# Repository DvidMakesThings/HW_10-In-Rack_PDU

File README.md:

# ENERGIS - The Managed PDU Project for 10-Inch Rack

## Overview

The **10-Inch Rack PDU (Power Distribution Unit)** is a modular power management system designed for efficient control and monitoring of power in a
rack-mounted environment. The project includes a Main Board and a display board to handle switching and power management.

Update 05.2025: Since lot of people said, it would be nice to have a Non-230V-Version, I started to develop
the USB-C version of ENERGIS with USB PD Source functionality: [PDNode-600 Pro](https://github.com/DvidMakesThings/HW_PDNode-600-Pro)

## ENERGIS Video Series

A new ENERGIS video series is rolling out. Part 1 is live below; Parts 2–4 will follow soon.

| Part | Title | Video |
| --- | --- | :---: |
| 1 | Overview |  |
| 2 | Hardware deep dive - The Schematics |  |
| 3 | Hardware deep dive - PCB design and Assembly | Coming soon |
| 4 | Embedded development - firmware and interfaces | Coming soon |
| 5 | Testing and validation | Coming soon |

## Progress and news

### Latest Features

| Feature                   | Description                                                           | Status | Note |
| ---                       | ---                                                                   | --- | --- |
| Renamebable Channels      | Channels are marked as 1–8; add label functionality                   |  | See: [Control page](#control-page) |
| Preset features           | ENERGIS now offers 5 programmable presets to apply on output          |  | See: [Settings page](#settings-page) |
| Apply-On-Startup feature  | A saved preset can be set to be auto-applied on device startup        |  | See: [Settings page](#settings-page) |
| Offset Calibration        | Implement off-state auto-zero for 0.75–0.77V and 0.02–0.05A offsets   |  | - |
| Safety features           | Software based current limit and restricion policy implemented        |  | - |
| Sheet metal enclosure     | Manufacturing and assembly ready. No future revision for enclosure    |  | - |

### Currently working on

| Improvement               | Description                                                       | Status |
| ---                       | ---                                                               | --- |
| Production optimization   | Finalize assembly workflow and cost reduction                     |  |
| Extended testing          | Expand automated test coverage (I²C, SPI, long-term soak tests)   |  |
| Community feedback        | Incorporate suggestions and adapt design for wider use cases      |  |
| And even more debugging   | It survived the 24h test, but you can never test enough           |  |

### Development Phases (Hardware + Firmware)

| Hardware Phase                          | Status         | Firmware Phase                         | Status         |
| --------------------------------------- | -------------- | -------------------------------------- | -------------- |
| PCB Design for Rev1.0                   | ✅ Completed    | CONFIG file for HW description         | ✅ Completed    |
| Enclosure Design                        | ✅ Completed    | ILI4988 TFT LCD Driver                 | ✅ Completed    |
| Order PCB                               | ✅ Completed    | MCP23017 Display-Board Driver          | ✅ Completed    |
| Prototyping and Hardware Testing        | ✅ Completed    | MCP23017 Relay-Board Driver            | ✅ Completed    |
| Implementing Rev2.0                     | ✅ Completed    | W5500 Ethernet Driver                  | ✅ Completed    |
| Implementing Relay Board Rev2.1         | ✅ Completed    | CAT24C512 512K EEPROM Driver           | ✅ Completed    |
| Initial Firmware Development            | ✅ Completed    | Version Control and EEPROM Data        | ✅ Completed    |
| Final PCB Revision                      | ✅ Completed    | Display Functions                      | ✅ Completed    |
| Enclosure Testing & Ventilation         | ✅ Completed    | System Startup Script                  | ✅ Completed    |
| Power Monitoring                        | ✅ Completed    | Multicore processing and RTOS          | ✅ Completed    |
| Production Optimization                 | 🔵 Planned      | Pushbutton control                     | ✅ Completed    |
| -                                       | -               | HLW8032 Power Monitor Dirver           | ✅ Completed    |
| -                                       | -               | Make Everything work together          | ✅ Completed    |
| -                                       | -               | HTML Server Implementation             | ✅ Completed    |
| -                                       | -               | Software debugging                     | ✅ Completed    |
| -                                       | -               | Ethernet based firmware update         | ❌ Not Possible |

---

## Specifications (EU, IEC/ENEC)

### Electrical Characteristics

* **Input:** 230 V AC, **10 A max**
* **Output Voltage:** 230 V AC
* **Total Output Current (all channels combined):** **10 A max**
* **Per-Channel Output Current:** **10 A max per active channel**, with **total combined output limited to 10 A**
* **Internal Power Supply:** 12 V, 1.5 A SMPS
* **Derived Internal Voltages:** 5 V and 3.3 V regulated from 12 V

### Relay Output Ratings

* **Common AC Trace Handling:** 16A max
* **Per-Relay Trace Rating:** 16A max
* **Relay Contact Rating:** 16A max

### Control and Driving Circuit

* **Relay Driver:** ULN2803 Darlington Array
* **Driving Current:** 33 mA per relay

## Specifications (US/Canada, UL/CSA)

### Electrical Characteristics

* **Input:** 250 V AC, **15 A max**
* **Output Voltage:** 250 V AC
* **Total Output Current (all channels combined):** **15 A max**
* **Per-Channel Output Current:** **15 A max per active channel**, with **total combined output limited to 15 A**
* **Internal Power Supply:** 12 V, 1.5 A SMPS
* **Derived Internal Voltages:** 5 V and 3.3 V regulated from 12 V

### Relay Output Ratings

* **Common AC Trace Handling:** 16 A max
* **Per-Relay Trace Rating:** 16 A max
* **Relay Contact Rating:** 16 A max

### Control and Driving Circuit

* **Relay Driver:** ULN2803 Darlington Array
* **Driving Current:** 33 mA per relay

---

## Features

- **Main Board:** Handles Ethernet communication, power conversion, and system logic. Manages AC switching with 8x 230V relays and safety
  isolation.
- **Display Board:** Headless mode, possible manual control with push buttons and real-time LED feedback
- **Ethernet Connectivity:** Uses the W5500 SPI-based Ethernet chip for remote
  control and monitoring via SNMPv1 and/or Web-UI. Supports DHCP with automatic
  link-local fallback and zero-config discovery by name (`energis.local` / `energis`)
  via mDNS and NetBIOS; IP changes apply live without a reboot.
- **Power Measurement:** AC voltage and current sensing for monitoring.
- **Sheetmetal Enclosure:** Designed for 10-inch rack mounting with front and rear access.

--- 

## Schematics

The full schematics for each board are available:

- **[Main Board Schematics](src/PDF/ENERGIS-1.1.0_mainBoard_schematics.pdf)**
- **[Display Board Schematics](src/PDF/ENERGIS-1.1.0_displayBoard_schematics.pdf)**

---

## Hardware Stackup

<table>
  <tr>
    <td align="center">
      
      <br><b>Main Board Top</b>
    </td>
    <td align="center">
      
      <br><b>Main Board Bottom</b>
    </td>
  </tr>
  <tr>
    <td align="center">
      
      <br><b>Display Board Top</b>
    </td>
    <td align="center">
      
      <br><b>Display Board Bottom</b>
    </td>
  </tr>
  <tr>
    <td align="center">
      
      <br><b>PEM Adapter</b>
    </td>
    <td align="center">
      
      <br><b>PEM Adapter</b>
    </td>
  </tr>
</table>

## Enclosure

The **Energis** PDU enclosure is built from **Aluminum 5052 sheet metal** with a thickness of **1.5 mm**, ensuring both durability and lightweight construction. It follows a **10-inch rack form factor (1U height)** with custom mounting brackets and integrated cutouts for AC input, Ethernet, USB-C, status LEDs, and IEC outlets.

Key specifications:
* **Material:** Aluminum 5052, 1.5 mm
* **Finish:** Powder coat (matte black, process black)
* **Threads & tapped holes:** Yes (no inserts, no welding)
* **Marking:** Laser engraved front and back panel labeling
* **Design:** Precision CNC cut and bent sheet metal, matte black powder-coated for protection and aesthetics

<br></br>
<div style="display: flex; gap: 24px; justify-content: center; align-items: flex-start; margin-bottom: 24px;">

</div>

<br></br>
Mounting options:
* **Desktop use** without brackets  
* **10-inch rack mounting** 

---

## Web UI

The ENERGIS now includes a lightweight embedded Web-UI for configuration and control.

## Control page

## Settings page

---

## Tests

Automated hardware and firmware validation is now integrated into **ENERGIS**.  
Test reports are published through **GitHub Pages** for transparent, reproducible verification.

All tests are executed using my **Universal Test Framework (UTFW)**, a custom Python-based automation framework, developed for hardware and firmware validation.  
UTFW provides deterministic test sequencing, automated setup and teardown, structured logging, analysis, and unified HTML/XML reporting.  
The nightly regression runs every individual test together to verify overall system stability and catch integration issues early.

---

### Nightly Regression Suite
Comprehensive end-to-end system test covering:
- UART communication  
- SNMP protocol  
- Web interface (PCAP)  
- EEPROM persistence  
- Power monitoring (HLW8032)  
- ADC/thermal sanity checks  
- Relay stress switching  

**[Latest Regression Report](https://dvidmakesthings.github.io/HW_10-In-Rack_PDU/Tests/Nightly_regression/test_suite_Nightly_Tests_20251005_232014.html)**

---

### Individual Test Reports
- [Serial Communication Test Report (HTML)](https://dvidmakesthings.github.io/HW_10-In-Rack_PDU/Tests/report_tc_serial_utfw/tc_serial_utfw_report.html)
- [Network SNMP Test Report (HTML)](https://dvidmakesthings.github.io/HW_10-In-Rack_PDU/Tests/report_tc_network_snmp/tc_network_snmp_report.html)
- [Network PCAP Analysis Report (HTML)](https://dvidmakesthings.github.io/HW_10-In-Rack_PDU/Tests/report_tc_network_pcap/tc_network_pcap_report.html)
- [PCAP Capture Test Report (HTML)](https://dvidmakesthings.github.io/HW_10-In-Rack_PDU/Tests/report_tc_pcap_capture/tc_pcap_capture_report.html)
- [Power Monitoring Test Report (HLW8032) (HTML)](https://dvidmakesthings.github.io/HW_10-In-Rack_PDU/Tests/report_tc_power_hlw8032/tc_power_hlw8032_report.html)
- [EEPROM Persistence Test Report (HTML)](https://dvidmakesthings.github.io/HW_10-In-Rack_PDU/Tests/report_tc_eeprom_persistence/tc_eeprom_persistence_report.html)
- [Sanity Check Test Report (HTML)](https://dvidmakesthings.github.io/HW_10-In-Rack_PDU/Tests/report_tc_sanity_check/tc_sanity_check_report.html)
- [Relay Stress Switching Test Report (HTML)](https://dvidmakesthings.github.io/HW_10-In-Rack_PDU/Tests/report_tc_stress_switching/tc_stress_switching_report.html)

---

### Changelog:
#### Rev0.1.0:
- Initial desing

#### Rev0.2.0:
- Correct all hardware related bugs
- Display-Board Rev0.2.0: 
    - Buttons too close to each-other. Manual control is uncomfortable 
    - MCP23S17 seems like unreachable, invertory shortage everywhere. Change to MCP23017
- Controller-Board Rev0.2.0: 
    - W5500 crystal wiring bug. 
    - v1.0 connectors replaced to smaller FFC ones
- Relay-Board Rev0.2.0: 
    - Add HLW8032 for power monitoring
    - Replace Flyback converter to a cheaper - ready made AC-DC converter unit

#### Rev0.2.1:
- Relay-Board Rev0.2.1: 
    - Capacitive dropper does not have enough power to supply 8xHLW8032 - Non-Isolated  buck converter implemented
- Display-Board Rev0.2.1:
    - Planned revision without the LCD. This is the main size issue, going to do a version where the setup fits in 1U size. 
    Currently for debug purposes 1.5U is perfectly fine

#### ENERGIS 1.0.0 
- Relay-Board and Controller Board is now combined: Main Board
- Added enable functionality to the PSU
- Added high precision LDO to supply the MCU
- Additional fan is possible, but the temperature doesn't go above 36°C

#### ENERGIS 1.1.0
- Cleaned up routing both for Display- and Main board
- NEW: PEM-Adapter: Unfortunately the commercially available Power Entry Modules are using bussed topology, seems like it's
impossible to buy snap-in modules with individual L/N control. The only possibility I've found is the 3-104-370 from Schurter, but
it's a PCB-mountable version. Using a small adapter board to hook the solder joints to faston connectors seems to be the only possibility

### Firmware Changelog
#### Firmware 1.2.0
- NEW: Live network reconfiguration: IP, subnet, gateway, DNS and DHCP mode changes apply on the fly, no reboot
- NEW: Software DHCP client (DORA) with DHCP hostname registration (option 12)
- NEW: Automatic link-local (APIPA, 169.254.x.y) fallback when DHCP finds no server
- NEW: Zero-config name resolution via mDNS (`energis.local`) and NetBIOS (`energis`)
- NEW: Per-unit unique name derived from the MAC (`energis-<mac>`) to avoid collisions, with the generic `energis` kept as an alias
- Web Settings: DHCP toggle; IP fields grey out when DHCP is enabled
- Console: `SET_DHCP` command; `NETINFO` now reports the live active IP and name
- Fixes: DHCP renewal loop with very long leases; name responders restored after cable re-plug/standby-exit

## License
### Software Components
This project's software is licensed under the **GNU Affero General Public License v3.0 (AGPL-3.0)**.
See the [Software License](LICENSE-AGPL) file for details.

#### What AGPL-3.0 means:

- ✅ **You can** freely use, modify, and distribute this software
- ✅ **You can** use this project for personal, educational, or internal purposes
- ✅ **You can** contribute improvements back to this project

- ⚠️ **You must** share any modifications you make if you distribute the software
- ⚠️ **You must** release the source code if you run a modified version on a server that others interact with
- ⚠️ **You must** keep all copyright notices intact

- ❌ **You cannot** incorporate this code into proprietary software without sharing your source code
- ❌ **You cannot** use this project in a commercial product without either complying with AGPL or obtaining a different license

### Hardware Components
Hardware designs, schematics, and related documentation are licensed under the **Creative Commons Attribution-NonCommercial-ShareAlike 4.0 International License (CC BY-NC-SA 4.0)**. See the [Hardware License](LICENSE-CC-BY-NC-SA) file for details.

#### What CC BY-NC-SA 4.0 means:

- ✅ **You can** study, modify, and distribute the hardware designs
- ✅ **You can** create derivative works for personal, educational, or non-commercial use
- ✅ **You can** build this project for your own personal use

- ⚠️ **You must** give appropriate credit and indicate if changes were made
- ⚠️ **You must** share any modifications under the same license terms
- ⚠️ **You must** include the original license and copyright notices

- ❌ **You cannot** use the designs for commercial purposes without explicit permission
- ❌ **You cannot** manufacture and sell products based on these designs without a commercial license
- ❌ **You cannot** create closed-source derivatives for commercial purposes
- ❌ **You cannot** use the designer's trademarks without permission

### Commercial & Enterprise Use

Commercial use of this project is prohibited without obtaining a separate commercial license. If you are interested in:

- Manufacturing and selling products based on these designs
- Incorporating these designs into commercial products
- Any other commercial applications

Please contact me through any of the channels listed in the [Contact](#contact) section to discuss commercial licensing arrangements. Commercial licenses are available with reasonable terms to support ongoing development.

## Contact

For questions or feedback:
- **Email:** [dvidmakesthings@gmail.com](mailto:dvidmakesthings@gmail.com)
- **GitHub:** [DvidMakesThings](https://github.com/DvidMakesThings)

## Contributing

Contributions are welcome! As this is an early-stage project, please reach out before 
making substantial changes:

1. Fork the repository
2. Create a feature branch (`git checkout -b feature/concept`)
3. Commit your changes (`git commit -m 'Add concept'`)
4. Push to the branch (`git push origin feature/concept`)
5. Open a Pull Request with a detailed description

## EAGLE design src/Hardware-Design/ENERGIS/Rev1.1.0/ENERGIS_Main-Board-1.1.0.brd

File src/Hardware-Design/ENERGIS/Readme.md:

# HLW8032 Upper-Bank Routing Issue — Fixed in HW 1.0.1

## Summary
On **hardware rev 1.0.0**, the measurement path for channels **5–8** is cross-routed at the optocouplers, mirroring the upper nibble. Relays/buttons are unaffected; only measurement presentation would be wrong without compensation.

## Symptom (on HW 1.0.0)
- Turning **CH5–CH8** on shows their voltage/current under the wrong rows in the UI.

| Logical Channel | Routed To (HW 1.0.0) |
|---:|:---|
| 5 | 8 |
| 6 | 7 |
| 7 | 6 |
| 8 | 5 |

## Root Cause
- PCB routing in the optocoupler stage crosses TX lines for channels 5–8.

## Software Handling
- The firmware checks board revision **at compile time** (`SW_REV == 100`) and applies a **MUX-select compensation** only for HW 1.0.0 (invert A/B when the C bit is set).
- Cache indices and UI mapping remain **identity**.
- **Result:** No user-visible issue on any build.

## Hardware Status
- **HW 1.0.1:** Routing corrected (1:1). The firmware automatically **disables** compensation on ≥1.0.1.
- **HW 1.0.0:** Fully functional due to firmware compensation.

## Verification
1. Switch on CH5…CH8 individually.  
2. Confirm the UI shows the correct channel voltage/current on both HW 1.0.0 (with compensation) and HW 1.0.1 (native).

---
**Status:** Fixed in hardware (rev 1.0.1). Software safeguard ensures no impact on users.

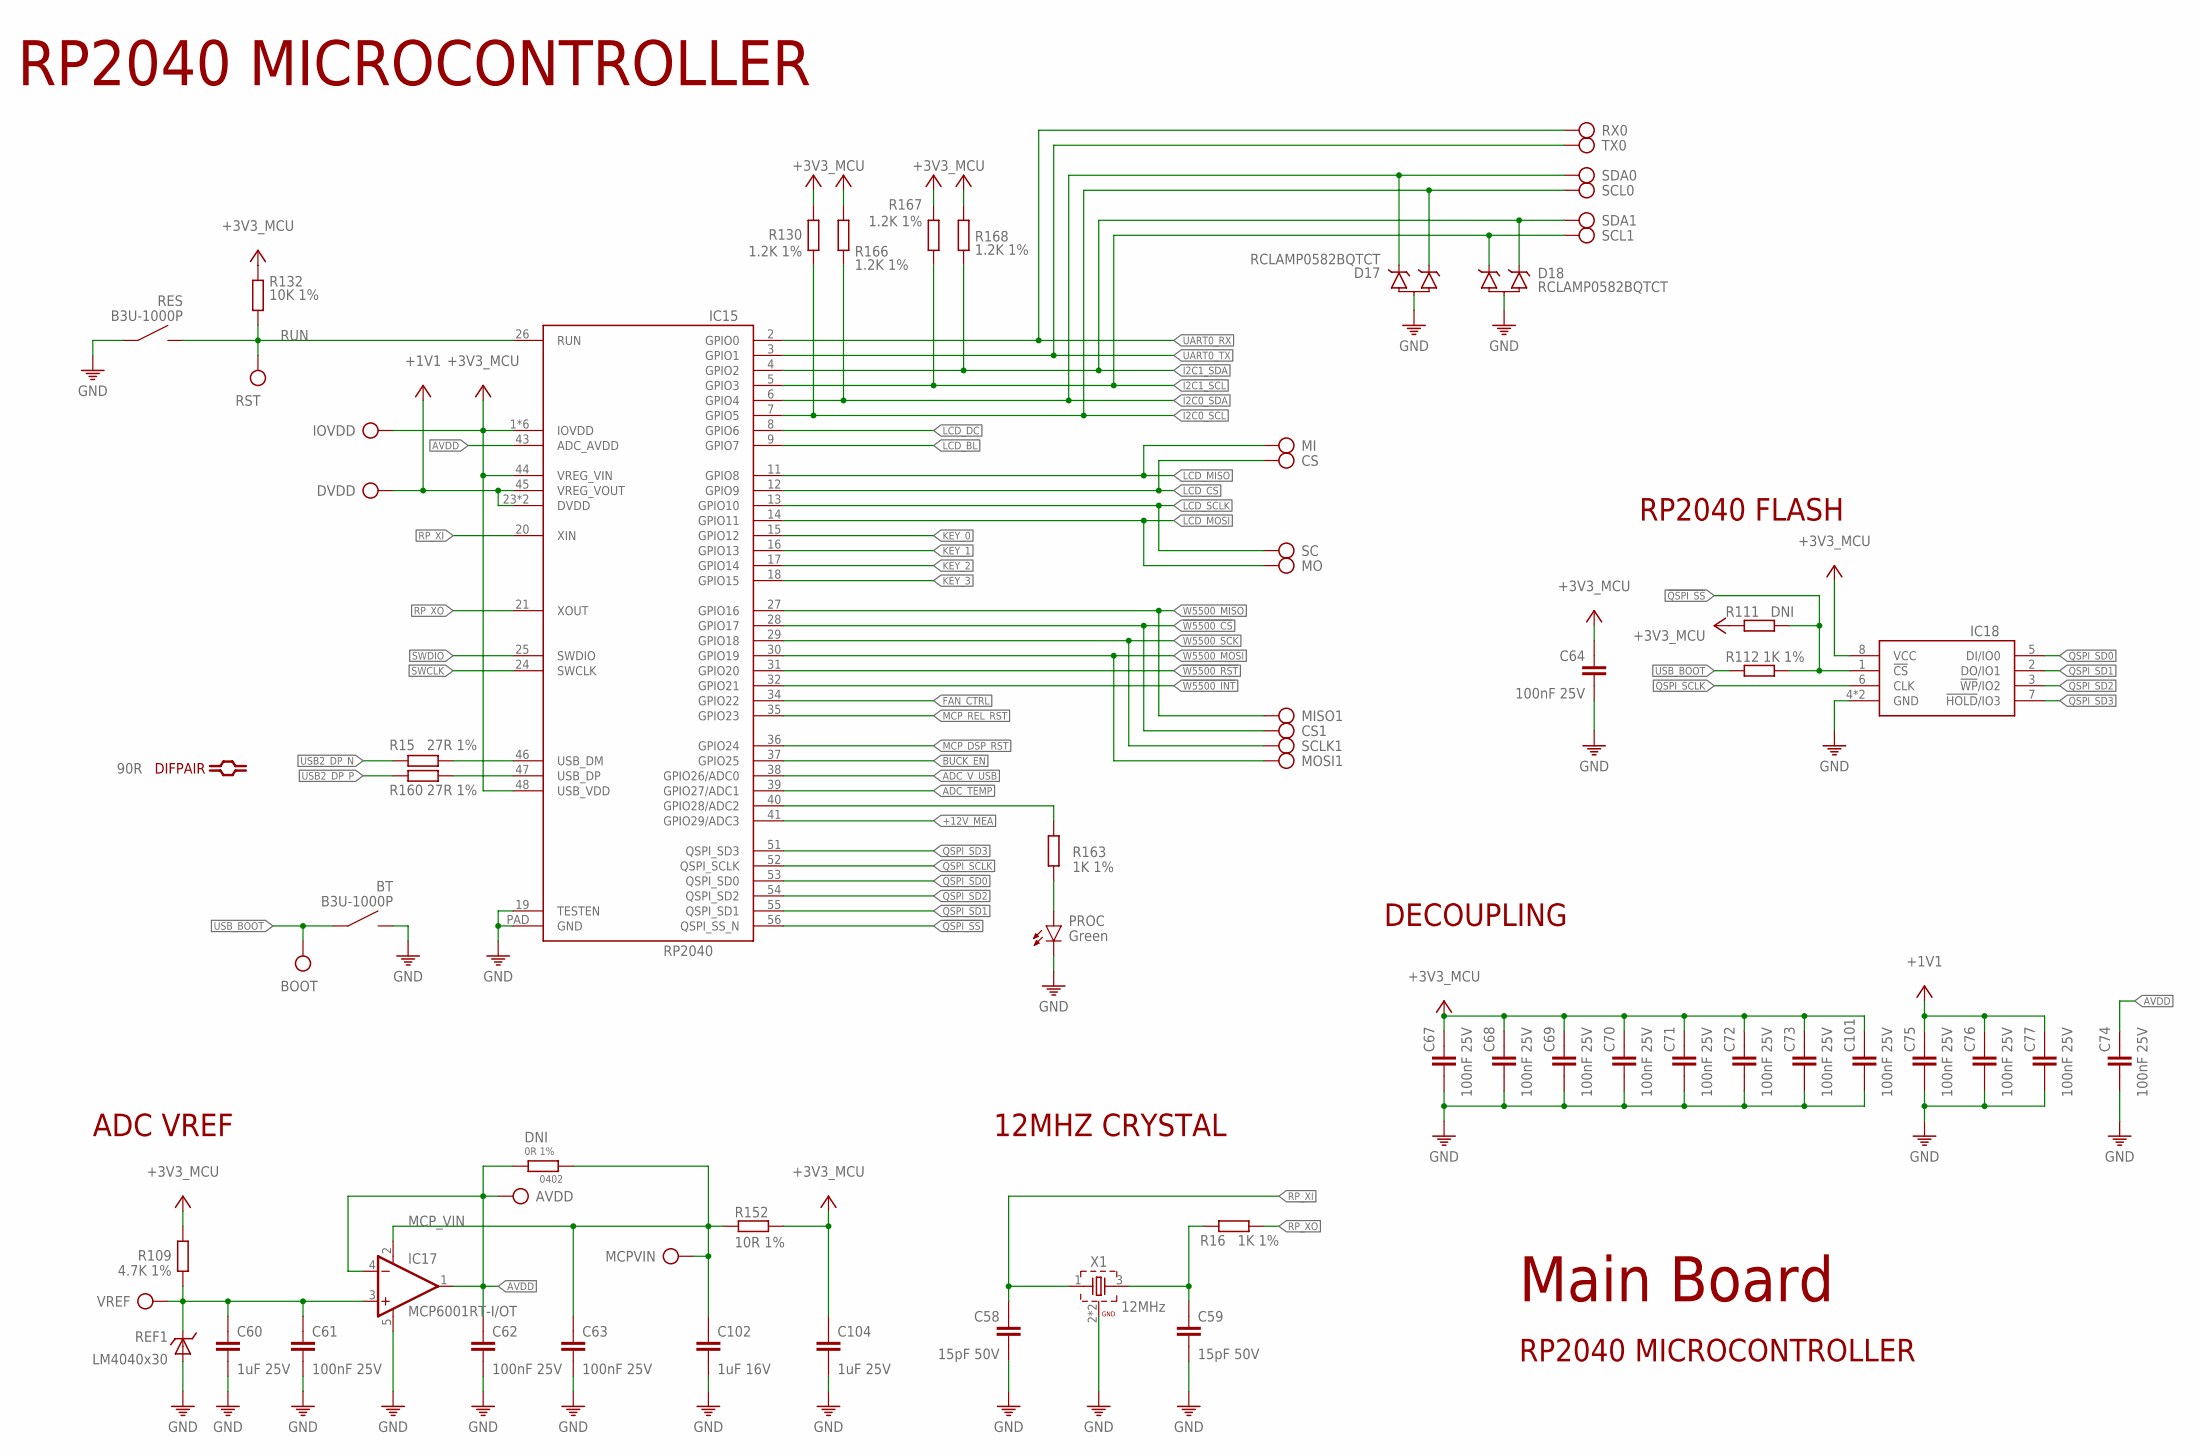
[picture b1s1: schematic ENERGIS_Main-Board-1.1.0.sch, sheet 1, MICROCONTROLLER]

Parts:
AVDD: DNI; TP-ROUND
BOOT: DNI; TP-ROUND
BT: B3U-1000P
C58, C59: 15pF 50V; 0201
C60, C104: 1uF 25V; 0402
C61, C62, C63, C64, C67, C68, C69, C70, C71, C72, C73, C74, C75, C76, C77, C101: 100nF 25V; 0201
C102: 1uF 16V; 0201
CS, CS1: DNI; TP-ROUND
D17, D18: RCLAMP0582BQTCT; SC75
DNI: 0R 1%; 0402
DVDD: DNI; TP-ROUND
IC15: RP2040; QFN56
IC17: MCP6001RT-I/OT; SOT23-5
IC18: W25Q128JVPIQ; SON127P600X500X75-8N
IOVDD: DNI; TP-ROUND
MCPVIN: DNI; TP-ROUND
MI: DNI; TP-ROUND
MISO1: DNI; TP-ROUND
MO: DNI; TP-ROUND
MOSI1: DNI; TP-ROUND
PROC: Green; LED-0603
R15, R160: 27R 1%; 0201
R16: 1K 1%; 0201
R109: 4.7K 1%; 0201
R111: DNI; R0201
R112, R163: 1K 1%; 0402
R130, R166, R167, R168: 1.2K 1%; 0402
R132: 10K 1%; 0402
R152: 10R 1%; 0201
REF1: LM4040x30; SOT23
RES: B3U-1000P
RST: DNI; TP-ROUND
RX0: DNI; TP-ROUND
SC: DNI; TP-ROUND
SCL0, SCL1: DNI; TP-ROUND
SCLK1: DNI; TP-ROUND
SDA0, SDA1: DNI; TP-ROUND
TX0: DNI; TP-ROUND
VREF: DNI; TP-ROUND
X1: 12MHz; WE-XTAL_CFPX-180

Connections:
!QSPI_SS: IC15.56 (QSPI_SS_N), IC18.1 (!CS), R111.1, R112.2
!W5500_CS: CS1.TP, IC15.28 (GPIO17); also elsewhere on the board
!W5500_INT: IC15.32 (GPIO21); also elsewhere on the board
!W5500_RST: IC15.31 (GPIO20); also elsewhere on the board
+1V1: C75.1, C76.1, C77.1, DVDD.TP, IC15.23 (DVDD), IC15.45 (VREG_VOUT), IC15.50 (DVDD)
+3V3_MCU: C64.1, C67.1, C68.1, C69.1, C70.1, C71.1, C72.1, C73.1, C101.1, C104.1, IC15.1 (IOVDD), IC15.10 (IOVDD), IC15.22 (IOVDD), IC15.33 (IOVDD), IC15.42 (IOVDD), IC15.44 (VREG_VIN), IC15.48 (USB_VDD), IC15.49 (IOVDD), IC18.8 (VCC), IOVDD.TP, R109.2, R111.2, R130.1, R132.1, R152.1, R166.1, R167.1, R168.1; also elsewhere on the board
+12V_MEA: IC15.41 (GPIO29/ADC3); also elsewhere on the board
ADC_TEMP: IC15.39 (GPIO27/ADC1); also elsewhere on the board
ADC_V_USB: IC15.38 (GPIO26/ADC0); also elsewhere on the board
AVDD: AVDD.TP, C62.1, C74.1, DNI.1, IC15.43 (ADC_AVDD), IC17.1 (OUT), IC17.4 (-IN)
BUCK_EN: IC15.37 (GPIO25); also elsewhere on the board
FAN_CTRL: IC15.34 (GPIO22); also elsewhere on the board
GND: BT.2, C58.2, C59.2, C60.2, C61.2, C62.2, C63.2, C64.2, C67.2, C68.2, C69.2, C70.2, C71.2, C72.2, C73.2, C74.2, C75.2, C76.2, C77.2, C101.2, C102.2, C104.2, D17.3, D18.3, IC15.19 (TESTEN), IC15.PAD (GND), IC17.5 (V-), IC18.4 (GND), IC18.PAD (GND), PROC.C, REF1.2 (A), REF1.3 (A), RES.1, X1.2 (GND), X1.4 (GND); also elsewhere on the board
I2C0_SCL: D17.1, IC15.7 (GPIO5), R130.2, SCL0.TP; also elsewhere on the board
I2C0_SDA: D17.2, IC15.6 (GPIO4), R166.2, SDA0.TP; also elsewhere on the board
I2C1_SCL: D18.2, IC15.5 (GPIO3), R167.2, SCL1.TP; also elsewhere on the board
I2C1_SDA: D18.1, IC15.4 (GPIO2), R168.2, SDA1.TP; also elsewhere on the board
KEY_0: IC15.15 (GPIO12); also elsewhere on the board
KEY_1: IC15.16 (GPIO13); also elsewhere on the board
KEY_2: IC15.17 (GPIO14); also elsewhere on the board
KEY_3: IC15.18 (GPIO15); also elsewhere on the board
LCD_BL: IC15.9 (GPIO7); also elsewhere on the board
LCD_CS: CS.TP, IC15.12 (GPIO9); also elsewhere on the board
LCD_DC: IC15.8 (GPIO6); also elsewhere on the board
LCD_MISO: IC15.11 (GPIO8), MI.TP; also elsewhere on the board
LCD_MOSI: IC15.14 (GPIO11), MO.TP; also elsewhere on the board
LCD_SCLK: IC15.13 (GPIO10), SC.TP; also elsewhere on the board
MCP_DSP_RST: IC15.36 (GPIO24); also elsewhere on the board
MCP_REL_RST: IC15.35 (GPIO23); also elsewhere on the board
MCP_VIN: C63.1, C102.1, DNI.2, IC17.2 (V+), MCPVIN.TP, R152.2
unnamed: IC15.40 (GPIO28/ADC2), R163.2
unnamed: PROC.A, R163.1
unnamed: C59.1, R16.1, X1.3 (2)
QSPI_SCLK: IC15.52 (QSPI_SCLK), IC18.6 (CLK)
QSPI_SD0: IC15.53 (QSPI_SD0), IC18.5 (DI/IO0)
QSPI_SD1: IC15.55 (QSPI_SD1), IC18.2 (DO/IO1)
QSPI_SD2: IC15.54 (QSPI_SD2), IC18.3 (!WP!/IO2)
QSPI_SD3: IC15.51 (QSPI_SD3), IC18.7 (!HOLD!/IO3)
RP_DP_N: IC15.46 (USB_DM), R15.2
RP_DP_P: IC15.47 (USB_DP), R160.2
RP_XI: C58.1, IC15.20 (XIN), X1.1
RP_XO: IC15.21 (XOUT), R16.2
RUN: IC15.26 (RUN), R132.2, RES.2, RST.TP; also elsewhere on the board
SWCLK: IC15.24 (SWCLK); also elsewhere on the board
SWDIO: IC15.25 (SWDIO); also elsewhere on the board
UART0_RX: IC15.2 (GPIO0), RX0.TP; also elsewhere on the board
UART0_TX: IC15.3 (GPIO1), TX0.TP; also elsewhere on the board
USB2_DP_N: R15.1; also elsewhere on the board
USB2_DP_P: R160.1; also elsewhere on the board
USB_BOOT: BOOT.TP, BT.1, R112.1
VREF: C60.1, C61.1, IC17.3 (+IN), R109.1, REF1.1 (C), VREF.TP
W5500_MISO: IC15.27 (GPIO16), MISO1.TP; also elsewhere on the board
W5500_MOSI: IC15.30 (GPIO19), MOSI1.TP; also elsewhere on the board
W5500_SCK: IC15.29 (GPIO18), SCLK1.TP; also elsewhere on the board

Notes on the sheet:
DECOUPLING
RP2040 MICROCONTROLLER
Main Board
RP2040 FLASH
12MHZ CRYSTAL
ADC VREF

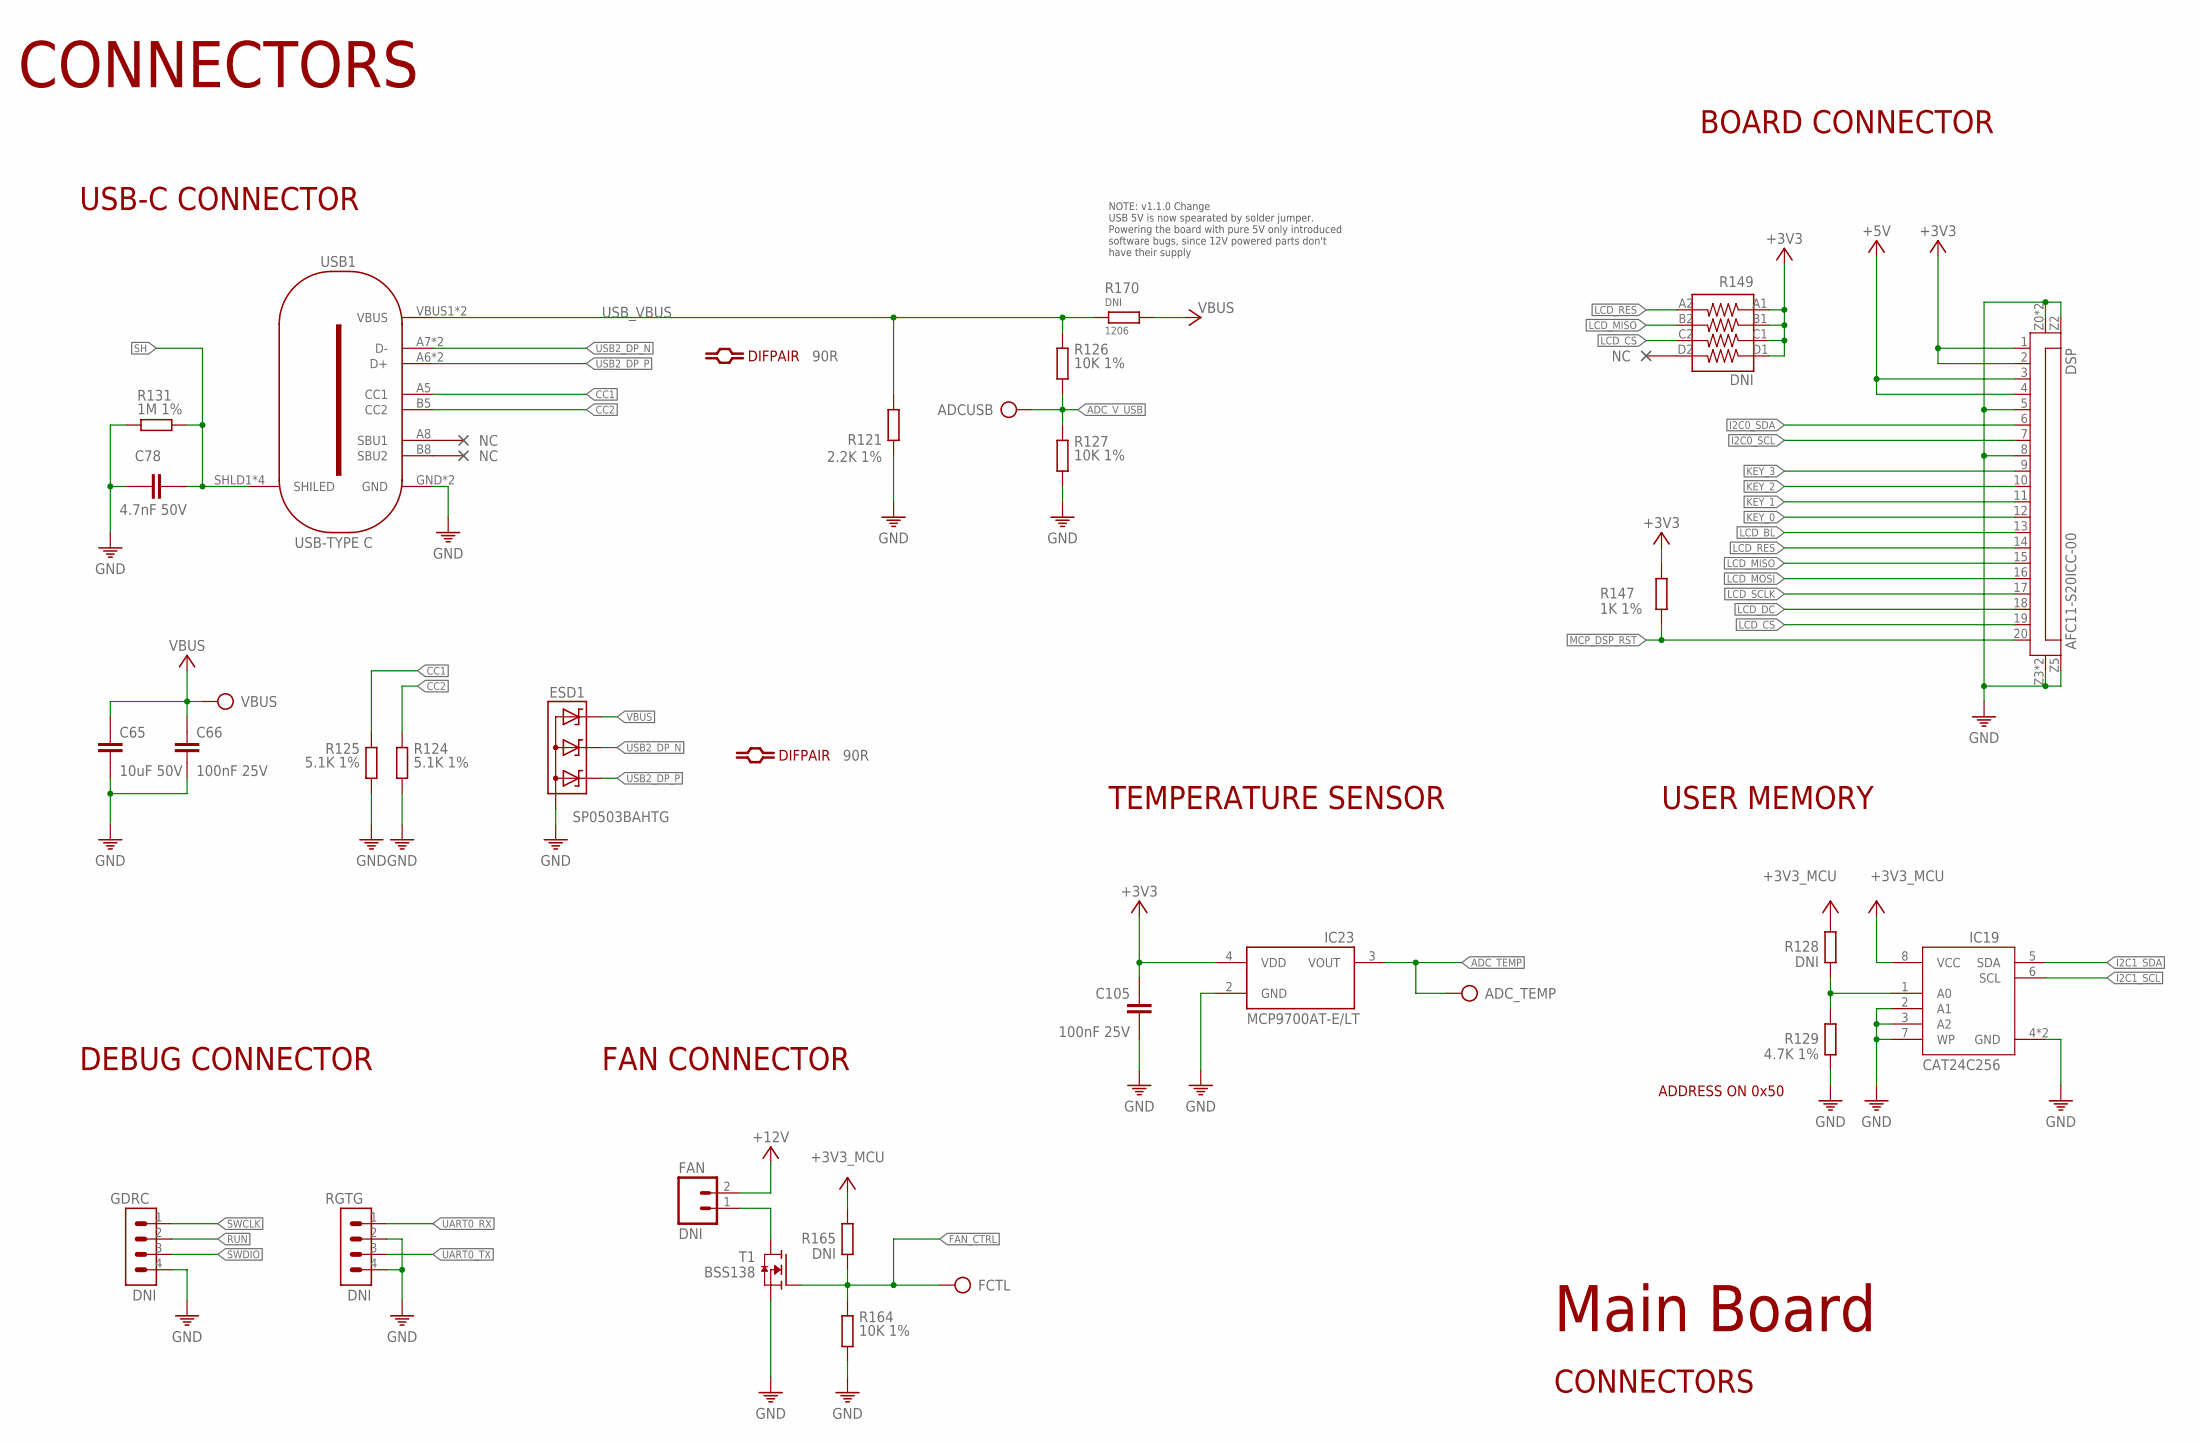
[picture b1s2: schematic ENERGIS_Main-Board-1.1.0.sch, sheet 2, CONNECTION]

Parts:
ADCUSB: DNI; TP-ROUND
ADC_TEMP: DNI; TP-ROUND
C65: 10uF 50V; 0805
C66: 100nF 25V; 0402
C78: 4.7nF 50V; 0402
C105: 100nF 25V; 0201
DSP: AFC11-S20ICC-00; FPC20
ESD1: SP0503BAHTG; SOT143
FAN: DNI; 02P
FCTL: DNI; TP-ROUND
GDRC: DNI; 1X4
IC19: CAT24C256HU4IGT3; SON50P300X200X50-9T130X140N
IC23: MCP9700AT-E/LT; SC70-5
R121: 2.2K 1%; 0201
R124, R125: 5.1K 1%; 0201
R126, R127: 10K 1%; 0201
R128, R165: DNI; R0201
R129: 4.7K 1%; 0201
R131: 1M 1%; 0402
R147: 1K 1%; 0402
R149: DNI; _0603X4-1206
R164: 10K 1%; 0402
R170: DNI; 1206
RGTG: DNI; 1X4
T1: BSS138; SOT23
USB1: USB-TYPE-C-018; USB-C
VBUS: DNI; TP-ROUND

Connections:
+3V3: C105.1, DSP.1, DSP.2, IC23.4 (VDD), R147.2, R149.A1 (1), R149.B1 (2), R149.C1 (3), R149.D1 (4); also elsewhere on the board
+3V3_MCU: IC19.8 (VCC), R128.2, R165.2; also elsewhere on the board
+5V: DSP.3, DSP.4; also elsewhere on the board
+12V: FAN.2; also elsewhere on the board
ADC_TEMP: ADC_TEMP.TP, IC23.3 (VOUT); also elsewhere on the board
ADC_V_USB: ADCUSB.TP, R126.2, R127.1; also elsewhere on the board
CC1: R125.1, USB1.A5 (CC1)
CC2: R124.1, USB1.B5 (CC2)
FAN_CTRL: FCTL.TP, R164.1, R165.1, T1.1 (G); also elsewhere on the board
GND: C65.2, C66.2, C78.2, C105.2, DSP.5, DSP.8, DSP.Z0 (Z1), DSP.Z1, DSP.Z2, DSP.Z3, DSP.Z4 (Z3), DSP.Z5 (Z4), ESD1.1 (A), GDRC.4, IC19.2 (A1), IC19.3 (A2), IC19.4 (GND), IC19.7 (WP), IC19.9 (GND), IC23.2 (GND), R121.2, R124.2, R125.2, R127.2, R129.1, R131.2, R164.2, RGTG.2, RGTG.4, T1.2 (S), USB1.GND, USB1.GND2 (GND); also elsewhere on the board
I2C0_SCL: DSP.7; also elsewhere on the board
I2C0_SDA: DSP.6; also elsewhere on the board
I2C1_SCL: IC19.6 (SCL); also elsewhere on the board
I2C1_SDA: IC19.5 (SDA); also elsewhere on the board
KEY_0: DSP.12; also elsewhere on the board
KEY_1: DSP.11; also elsewhere on the board
KEY_2: DSP.10; also elsewhere on the board
KEY_3: DSP.9; also elsewhere on the board
LCD_BL: DSP.13; also elsewhere on the board
LCD_CS: DSP.19, R149.C2 (6); also elsewhere on the board
LCD_DC: DSP.18; also elsewhere on the board
LCD_MISO: DSP.15, R149.B2 (7); also elsewhere on the board
LCD_MOSI: DSP.16; also elsewhere on the board
LCD_RES: DSP.14, R149.A2 (8)
LCD_SCLK: DSP.17; also elsewhere on the board
MCP_DSP_RST: DSP.20, R147.1; also elsewhere on the board
unnamed: FAN.1, T1.3 (D)
unnamed: IC19.1 (A0), R128.1, R129.2
RUN: GDRC.2; also elsewhere on the board
SH: C78.1, R131.1, USB1.SHLD1 (SHILED), USB1.SHLD2 (SHILED), USB1.SHLD3 (SHILED), USB1.SHLD4 (SHILED); also elsewhere on the board
SWCLK: GDRC.1; also elsewhere on the board
SWDIO: GDRC.3; also elsewhere on the board
UART0_RX: RGTG.1; also elsewhere on the board
UART0_TX: RGTG.3; also elsewhere on the board
USB2_DP_N: ESD1.3 (C2), USB1.A7 (D-), USB1.B7 (D-); also elsewhere on the board
USB2_DP_P: ESD1.2 (C1), USB1.A6 (D+), USB1.B6 (D+); also elsewhere on the board
USB_VBUS: R121.1, R126.1, R170.1, USB1.VBUS1 (VBUS), USB1.VBUS2 (VBUS)
VBUS: C65.1, C66.1, ESD1.4 (C3), R170.2, VBUS.TP; also elsewhere on the board

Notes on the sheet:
USB-C CONNECTOR
BOARD CONNECTOR
DEBUG CONNECTOR
FAN CONNECTOR
CONNECTORS
Main Board
NOTE: v1.1.0 Change USB 5V is now spearated by solder jumper. Powering the board with pure 5V only introduced software bugs, since 12V powered parts don't have their supply
USER MEMORY
TEMPERATURE SENSOR
ADDRESS ON 0x50

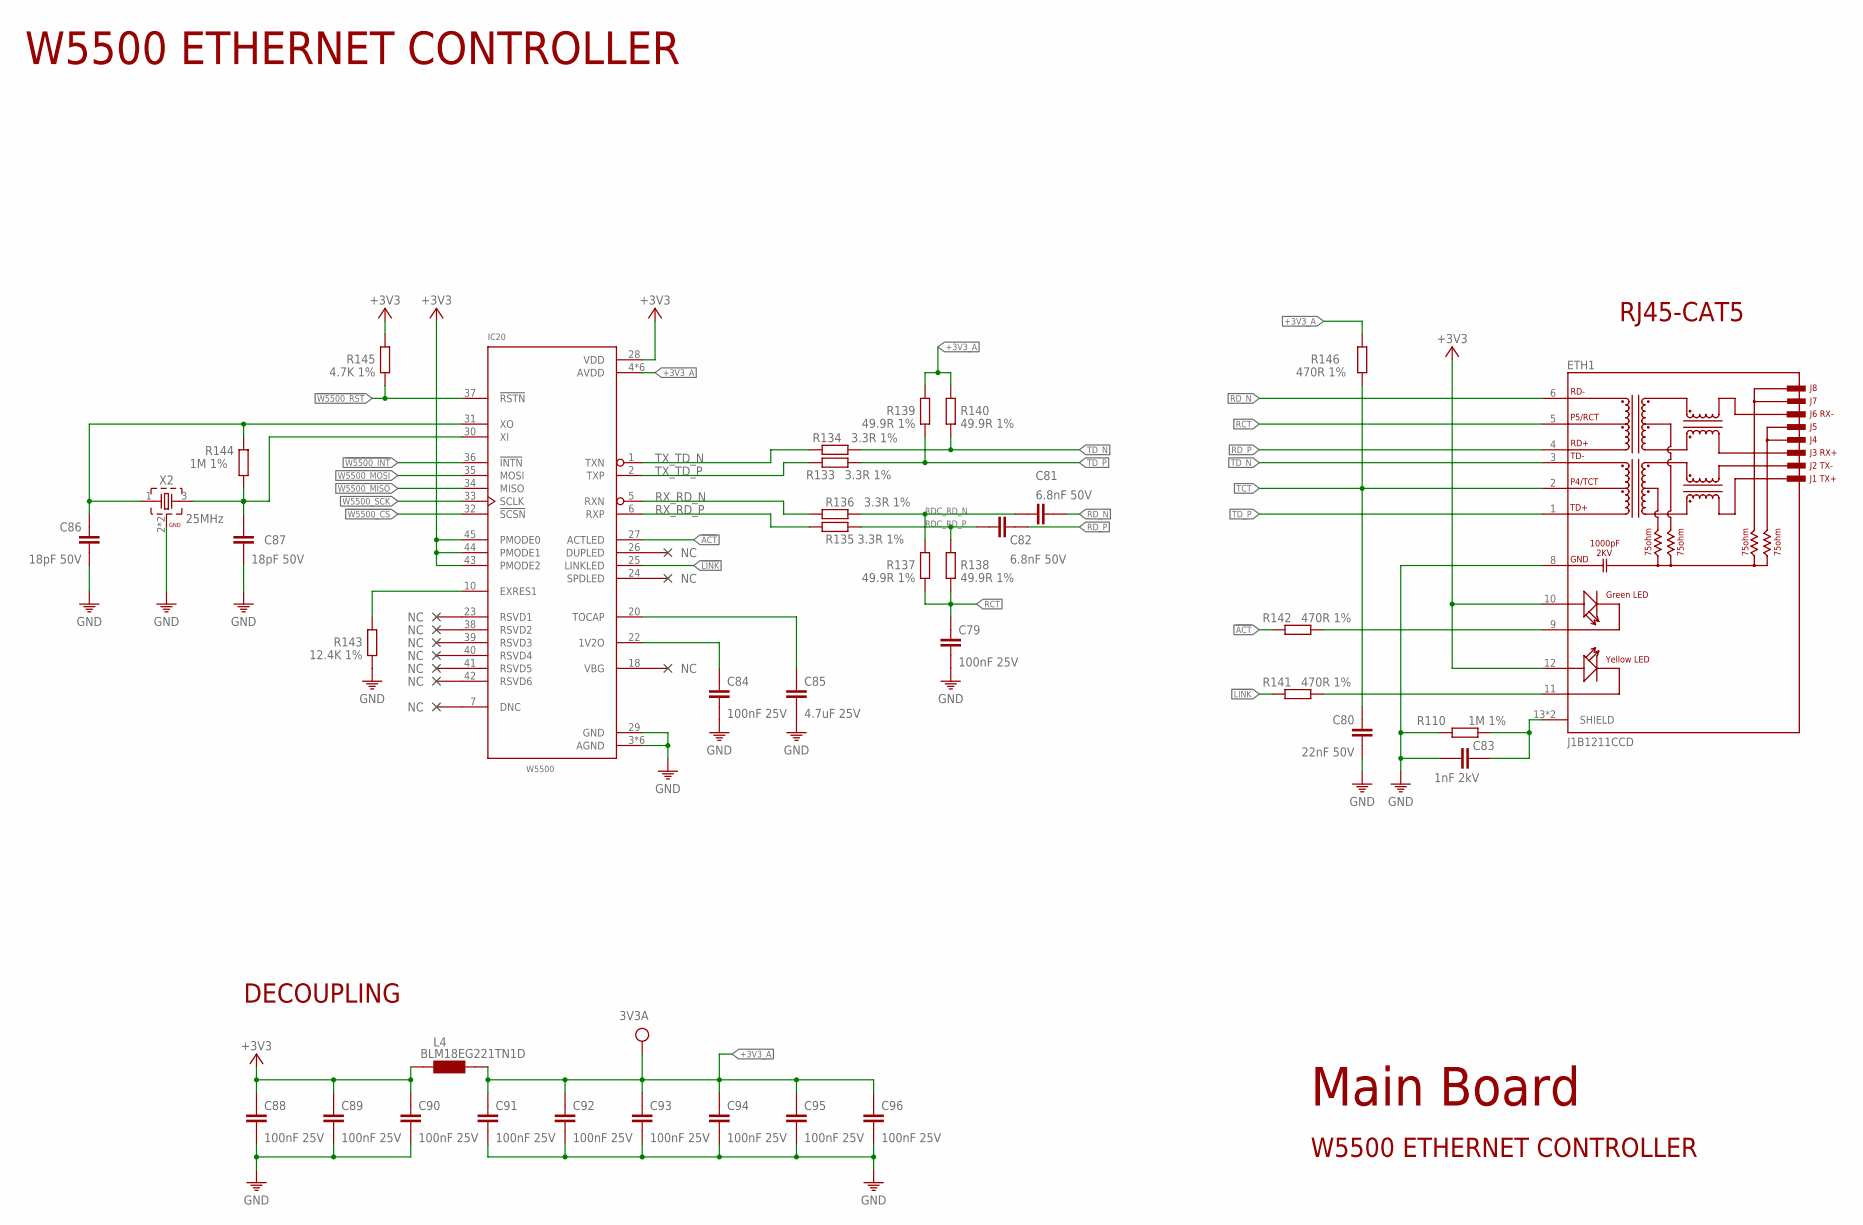
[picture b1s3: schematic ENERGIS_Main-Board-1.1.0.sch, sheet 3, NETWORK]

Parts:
3V3A: DNI; TP-ROUND
C79: 100nF 25V; 0402
C80: 22nF 50V; 0402
C81, C82: 6.8nF 50V; 0201
C83: 1nF 2kV; 1206
C84, C88, C89, C90, C91, C92, C93, C94, C95, C96: 100nF 25V; 0201
C85: 4.7uF 25V; 0402
C86, C87: 18pF 50V; 0201
ETH1: J1B1211CCD
IC20: W5500; LQFP48
L4: BLM18EG221TN1D; 0603
R110: 1M 1%; 1206
R133, R134, R135, R136: 3.3R 1%; 0201
R137, R138, R139, R140: 49.9R 1%; 0201
R141, R142, R146: 470R 1%; 0402
R143: 12.4K 1%; 0201
R144: 1M 1%; 0201
R145: 4.7K 1%; 0201
X2: 25MHz; WE-XTAL_CFPX-180

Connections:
!ACT: IC20.27 (ACTLED), R142.1
!LINK: IC20.25 (LINKLED), R141.1
!W5500_CS: IC20.32 (!SCSN); also elsewhere on the board
!W5500_INT: IC20.36 (!INTN); also elsewhere on the board
!W5500_RST: IC20.37 (!RSTN), R145.1; also elsewhere on the board
+3V3: C88.1, C89.1, C90.1, ETH1.10 (GREEN+), ETH1.12 (YELLOW+), IC20.28 (VDD), IC20.43 (PMODE2), IC20.44 (PMODE1), IC20.45 (PMODE0), L4.1, R145.2; also elsewhere on the board
+3V3_A: 3V3A.TP, C91.1, C92.1, C93.1, C94.1, C95.1, C96.1, IC20.4 (AVDD), IC20.8 (AVDD), IC20.11 (AVDD), IC20.15 (AVDD), IC20.17 (AVDD), IC20.21 (AVDD), L4.2, R139.2, R140.2, R146.2
GND: C79.2, C80.2, C83.1, C84.2, C85.2, C86.2, C87.2, C88.2, C89.2, C90.2, C91.2, C92.2, C93.2, C94.2, C95.2, C96.2, ETH1.8 (GND), IC20.3 (AGND), IC20.9 (AGND), IC20.14 (AGND), IC20.16 (AGND), IC20.19 (AGND), IC20.29 (GND), IC20.48 (AGND), R110.1, R143.1, X2.2 (GND), X2.4 (GND); also elsewhere on the board
unnamed: ETH1.11 (YELLOW-), R141.2
unnamed: ETH1.9 (GREEN-), R142.2
unnamed: IC20.10 (EXRES1), R143.2
unnamed: C84.1, IC20.22 (1V2O)
unnamed: C85.1, IC20.20 (TOCAP)
unnamed: C87.1, IC20.30 (XI), R144.1, X2.3 (2)
RCT: C79.1, ETH1.5 (P5/RCT), R137.1, R138.1
RDC_RD_N: C81.1, R136.2, R137.2
RDC_RD_P: C82.1, R135.2, R138.2
RD_N: C81.2, ETH1.6 (RD-)
RD_P: C82.2, ETH1.4 (RD+)
RX_RD_N: IC20.5 (RXN), R136.1
RX_RD_P: IC20.6 (RXP), R135.1
SH: C83.2, ETH1.13 (SHIELD), ETH1.14 (SHIELD), R110.2; also elsewhere on the board
TCT: C80.1, ETH1.2 (P4/TCT), R146.1
TD_N: ETH1.3 (TD-), R134.2, R140.1
TD_P: ETH1.1 (TD+), R133.2, R139.1
TX_TD_N: IC20.1 (TXN), R134.1
TX_TD_P: IC20.2 (TXP), R133.1
W5500_MISO: IC20.34 (MISO); also elsewhere on the board
W5500_MOSI: IC20.35 (MOSI); also elsewhere on the board
W5500_SCK: IC20.33 (SCLK); also elsewhere on the board
XO: C86.1, IC20.31 (XO), R144.2, X2.1

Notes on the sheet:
W5500 ETHERNET CONTROLLER
RJ45-CAT5
DECOUPLING
Main Board

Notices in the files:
parts and their libraries:
SparkFun-Aesthetics: Licensing: Creative Commons ShareAlike 4.0 International - https://creativecommons.org/licenses/by-sa/4.0
ds_trafo: Copyright: Würth Elektronik
COPYRIGHT: Copyright (C) 2025 Ultra Librarian. All rights reserved.
